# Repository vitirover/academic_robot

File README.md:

# Vitirover Academic Robot

🌿 The Vitirover Academic empowers students and researchers to operate a robot designed for complex outdoor environments, boasting exceptional energy management and a patented, uniquely engineered movement system. We provide detailed motion equations for an in-depth understanding.

## 🕹️ Control Options:

 - __Web Interface__: Intuitively control the robot through our [user-friendly web platform](https://cloud.vitirover.eu).
 - __Remote Scripting__: Use Scratch-like interface to program and execute remote scripts.
 - __Advanced Mode__: For the tech-savvy, dive into __Python__ coding or __ROS__ for granular control.

## 🔧 What's inside

 - Standard Vitirover Robot
 
 - Charger
 
 - Alimentation card to add you own electronics, detectors or motors. More information [here](./power_card/).

 - Jetson Nano : to operate the robot directly with your code. You could use any board (raspberry, etc.), but documentation will be provided for Jetson 

## 📡 API Features

Protobuf Technology: Utilizes Google's Protobuf for standardized, cross-language communication protocol encoding and decoding.

Data Frames:
 - __Telemetry Data__: Broadcasted by the robot at 10Hz, includes GPS, rear axle angle, motors status, and more.
 
 - __Control Commands__: Send direct instructions for individual motor control.

You can keep the two cameras connected to our electronics, or connect them to your board if you want to use Vision in you application.

The trame definitions with all fields are [here](protobuf/telemetry.proto)

# Getting started

## With the standard Vitirover web interface

 - Get a Vitirover robot through us or our distributors

 - Get a [Vitirover Cloud account](https://cloud.vitirover.eu) connected to this robot by first creating you account and contacting us to add the robot to your account

 - Push the Vitirover On/Off button at the back upward

 - Wait for the robot to connect. Its icon will turn yellow 🟡

 - In your robot page (click its name on the menu), you should be able to move the robot using the controller 🎮 icon on the map

  - You can activate the robot live view from its camera using the camera icon on the map 👁️ (only if cameras are connected to the main board)

 - In the Scripts section, try out Scratch-like scripts. Use Control blocks to move the robot. Experiment, but ensure the robot is on the ground to prevent falls.⚠️

 - Please consult the Vitirover help section in our cloud for using the standard robot functions ❓

## With the Jetson Nano included in the Academic robot

### Using SSH and a local network

The **VitiroverAP_[name of your robot]** network is intended for private use since it is emitted by our non-academic motherboard.

Starting at this commit, we include a **vitirover-wifi-manager** systemd service to help you getting remote access without the need to open the robot each time (see "direct access" section). When a wifi configuration is set up, it will be active even after a reboot.
The Jetson Nano, with the Wifi card we added, only supports one wifi connection at the time. But to be able to use this connection confortably, you will need to have an SSH connection and an internet access on the Jetson Nano simultaneously.
In order to accomplish this, the solution is to connect the Jetson Nano directly to your local wifi network, and get SSH access from your computer thought your local wifi network.

#### If vitirover-wifi-manager is installed (robots produced since this commit)

The "vitirover-wifi-manager" emits a hotspot network, **Vitirover-SSH**. Thought this network, you will configure the **local network** you want to use. Once this is done, you apply this configuration, SSH will cut, and you will be able to access SSH again thought your local-network.

- Start the robot and the Jetson Nano
- Connect to the **Vitirover-SSH** network. Password is **vitirover**
- use putty (on windows) or ssh on "vitirover@10.42.0.1" (port 22).
- cd ~/Desktop/academic_robot/
- sudo ./wifi_config_tools config
- follow instructions to configure your local wifi network to connect to (using a static ip address)
- reboot, the robot should be connected to your local wifi network using the IP adress you provided
- connect to the robot thought you local network with SSH (user and password are vitirover, port 22). Now you should have both a working SSH connection, AND access to internet (ping 8.8.8.8 to check)
- see python examples or ros repository (or installation folder where there are some examples) to begin

#### If vitirover-wifi-manager is not installed yet
You will have to use get direct access to the jetson nano (see next section), then : 
 - cd ~/Desktop/academic_robot/
 - git pull (or "git switch wifi-manager" if not merged yet)
 - cd vitirover-wifi-manager
 - chmod +x wifi_config_tools
 - chmod +x vitirover-wifi-manager
 - sudo ./wifi_config_tools install
 - sudo ./wifi_config_tools config
 - follow instructions to configure your local wifi network to connect to (using a static ip address)
 - reboot, the robot should be connected to your local wifi network
 - connect to the robot thought you local network with SSH (user and password are vitirover, port 22). Now you should have both SSH connection, AND access to internet (ping 8.8.8.8 to check)
- see python examples or ros repository to begin

### Direct access to the Jetson nano

If you struggle with the setup of the SSH connection and remote access, you can always connect directly on the jetson nano by : 
 - removing the ten screws with a M5 Allen Key (found on bike repair kits for example). Pay attention to not pull cables (GNSS antenna and power cable). It is practical to keep the upper hull on top, but turn it to access the Jetson Nano.
 - checking that the robot is on (button is up) and leds on the Jetson Nano are on
 - Connecting a computer screen via a Jetson HDMI port
 - Connecting a USB mouse, a keyboard to the Jetson
 - Log in : The default user and password is __vitirover__.****
 - This repository, and the [ROS repository](https://github.com/vitirover/vitirover_ws) are already present. If they are not up to date, you can do a **git pull** on them. 
 - In order to start, you can for example test python example scripts in examples, or head directly into the [ROS repository](https://github.com/vitirover/vitirover_ws)

### Network Schema
**Coming soon**

# Python example scripts

In order to control the robot directly from you code, you will need the Jetson Nano connected throught an USB/Ethernet adapter to our electronics JST ports.

See [the python basic example](/examples/basic-python-protobuf.py)

# Getting started: Jetson Nano

In the academic package you have a Jetson nano included. A Linux OS as well as some examples to use the robot are already pre-installed. 
If you want more informations on how to install your own setup you can refer to : [Nvidia](https://developer.nvidia.com/embedded/learn/get-started-jetson-nano-devkit#intro)

The password by default is "vitirover". Once you are logged in you can open Visual Studio Code (exactly : code-oss, the full open-source version) and navigate to academic_robot/examples. 

# How to use the Jetson nano remotely
## On Linux

In your package you can find a fake HDMI. This dongle allows you to visualize your Jetson Nano from your PC through the wifi card (that we added to the standard Jetson Nano). 

First, connect the Jetson Nano to your wifi. 

Install tightvnc on your PC (do it once only):
```
sudo apt install xtightvncviewer
```

Then start the server (modify your.ip.address with your IP address):

```
xtightvncserver your.ip.address
```
or 
```
/usr/bin/xtightvncserver your.ip.address
```

Connect to the jetson nano:
```
xtightvncviewer your.ip.address -compresslevel 9 -quality 4
```

Type your password, and you are logged into the Jetson Nano ;)

## Counter EMF to measure motor's rpm

The agricultural standards require high robustness due to operation in chaotic terrain. To measure the RPM of the wheels, we have utilized Back Electromotive Force (BEMF), which provides accurate RPM measurements suitable for outdoor environments. For academic purposes, an encoder kit is available, offering even more precise RPM measurements. For more information about the encoder kit, please visit [encoder kit](/encoder_kit).

# Contributing

We would be glad to hear from you, you contact us via issues for any questions about this repo.

This repository is constently evolving with new updates and more examples. Feel free to contribute to our community on the academic robot !

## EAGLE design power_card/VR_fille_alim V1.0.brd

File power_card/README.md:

## Power Board Overview 🌐

The power board features four terminal blocks, each providing a different maximum output voltage and current. Here are the specifications and maximum power calculations for each:

- **12V, 2A**  
  Maximum Power: `24W`
- **5V, 2A**  
  Maximum Power: `10W`
- **5V, 4A** (dedicated for powering the Jetson Nano, see above)  
  Maximum Power: `20W`
- **Battery Voltage (24V nominal), 6A**  
  Maximum Power: `144W`

Additionally, links to the EAGLE files for the power board are provided. These files include all necessary schematics and board designs in EAGLE format, ideal for modification or further development.

### Jetson Nano DC Power Jumper

As explained (but difficult to find) in the [Jetson Nano Developper Kit User Guide](https://developer.download.nvidia.com/assets/embedded/secure/jetson/Nano/docs/NV_Jetson_Nano_Developer_Kit_User_Guide.pdf?onc0KLg5WqXnycWsVxITqVJuQhOv7dOwZDn_6wMDd2yiHHP-d7uv_KwyZQFvdmQjeIwzmvuDMyNS2j6b7665m7rmn-Uv2NYOiBAWWCoRhCM5Xq7rqr0AOUHEIOBn2JpZgTdjgMTqyD2t5OOGEKS2ve_BtuEa8IP3TMF1NwbBa36ZujDmUTJMczagMmcFHalibv8=&t=eyJscyI6ImdzZW8iLCJsc2QiOiJodHRwczovL3d3dy5nb29nbGUuY29tLyJ9) and [on the jetson forum](https://forums.developer.nvidia.com/t/power-supply-considerations-for-jetson-nano-developer-kit/71637), for versions of the Jetson Nano with a Barrel Jack, you have to **connect the jumper** to the J48 pins to be able to power the board from this power supply. We connect it to ensure that everything is working before shipping the robot to you.
Similarly, if you want to power the Jetson from another power source, you have to **disconnect** the jumper.

### Safety Warning ⚠️

**Current Limitation:** The total current consumption across all systems connected to the board must not exceed 6A. Exceeding this limit will trigger a protective fuse, rendering the power board unusable.

**Connection Precautions:** It is crucial to follow the markings on the PCB. Ensure that the positive and negative terminals (GND) are not reversed when connecting any system to the terminal blocks.

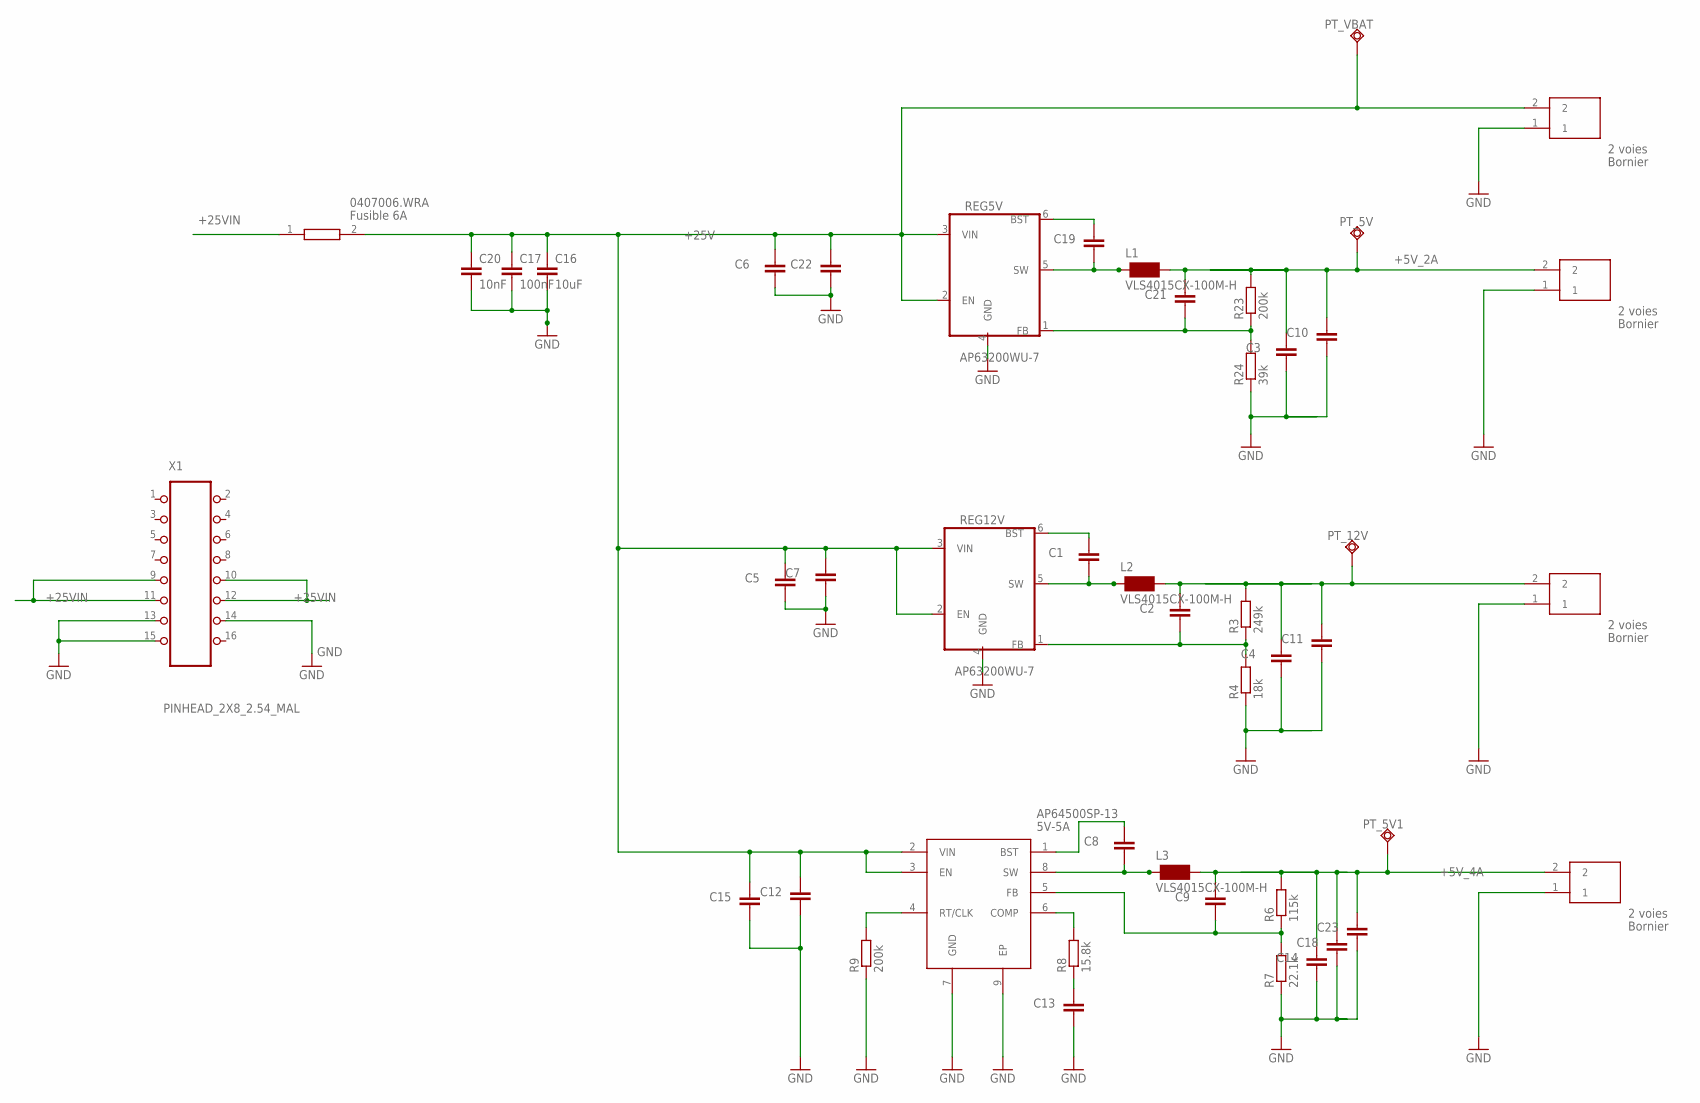
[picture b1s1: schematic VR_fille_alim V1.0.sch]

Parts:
C1, C5, C6, C8, C15, C19: 100nF; C0402
C2: 56pF; C0402
C3, C4, C10, C11, C14, C18, C23: 22uF; C0402
C7, C12, C22: 10uF; C0402
C9, C21: 100pF; C0402
C13: 2.7nF; C0402
C16: 10uF; C0805
C17: 100nF; C0805
C20: 10nF; C0805
F1: 0407006.WRA; FUSC3216X98N
IC1: AP64500SP-13; SOIC127P600X163-9N
J1, J2, J3, J5: 691214110002
L1, L2, L3: VLS4015CX-100M-H; VLS4015
PT_5V, PT_5V1, PT_12V: POINT_TEST
PT_VBAT: POINT_TEST
R3: 249k; R0402
R4: 18k; R0402
R6: 115k; R0402
R7: 22.1k; R0402
R8: 15.8k; R0402
R9, R23: 200k; R0402
R24: 39k; R0402
REG5V, REG12V: AP63200WU-7; TSOT26
X1: PINHEAD_2X8_2.54_MAL

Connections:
+5V_2A: C3.2, C10.2, C21.2, J1.2, L1.2, PT_5V.>NAME, R23.2
+5V_4A: C9.2, C14.2, C18.2, C23.2, J3.2, L3.2, PT_5V1.>NAME, R6.2
+12V_2A: C2.2, C4.2, C11.2, J2.2, L2.2, PT_12V.>NAME, R3.2
+25V: C5.2, C6.2, C7.2, C12.2, C15.2, C16.1, C17.1, C20.1, C22.2, F1.2, IC1.2 (VIN), IC1.3 (EN), J5.2, PT_VBAT.>NAME, REG5V.2 (EN), REG5V.3 (VIN), REG12V.2 (EN), REG12V.3 (VIN)
+25VIN: F1.1, X1.9, X1.10, X1.11, X1.12
GND: C3.1, C4.1, C5.1, C6.1, C7.1, C10.1, C11.1, C12.1, C13.1, C14.1, C15.1, C16.2, C17.2, C18.1, C20.2, C22.1, C23.1, IC1.7 (GND), IC1.9 (EP), J1.1, J2.1, J3.1, J5.1, R4.1, R7.1, R9.1, R24.1, REG5V.4 (GND), REG12V.4 (GND), X1.13, X1.14, X1.15
unnamed: C2.1, R3.1, R4.2, REG12V.1 (FB)
unnamed: C1.1, L2.1, REG12V.5 (SW)
unnamed: C1.2, REG12V.6 (BST)
unnamed: C9.1, IC1.5 (FB), R6.1, R7.2
unnamed: C8.1, IC1.8 (SW), L3.1
unnamed: C8.2, IC1.1 (BST)
unnamed: IC1.6 (COMP), R8.2
unnamed: C13.2, R8.1
unnamed: C21.1, R23.1, R24.2, REG5V.1 (FB)
unnamed: C19.1, L1.1, REG5V.5 (SW)
unnamed: C19.2, REG5V.6 (BST)
unnamed: IC1.4 (RT/CLK), R9.2

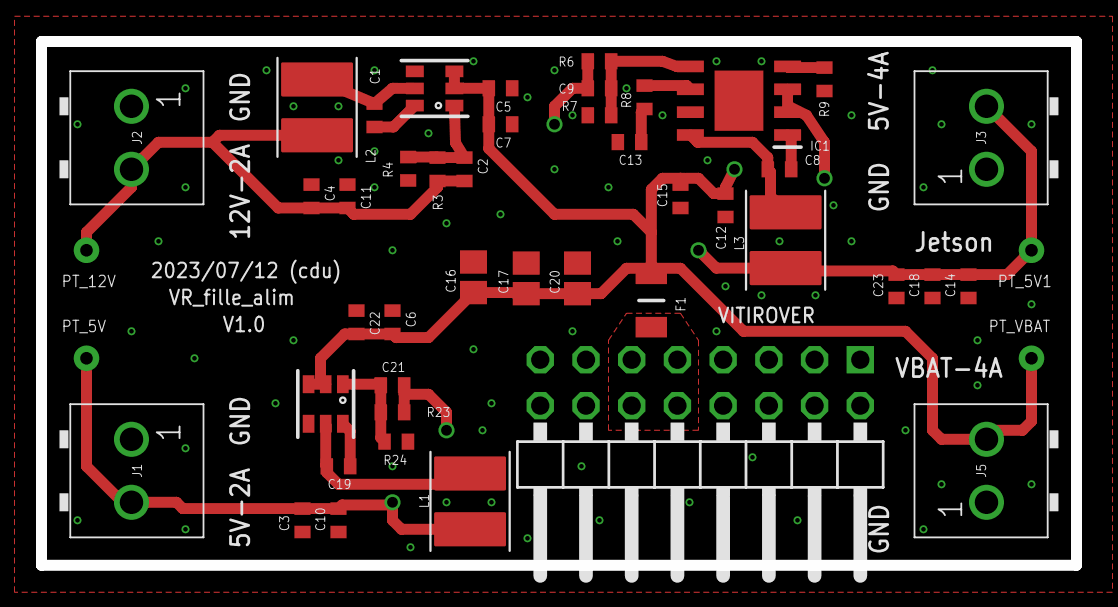
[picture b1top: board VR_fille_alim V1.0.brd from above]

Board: 4 copper layers, 57.5 x 29.1 mm, 47 parts (0 on the bottom side), 18 nets.

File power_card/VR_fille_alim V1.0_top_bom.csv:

Comment,Designator,Footprint,LCSC Part #
2.7nF,C13,C0402,
10nF,C20,C0805,
10uF,C7 C12,C0402,
10uF,C16,C0805,
10uF,C22,C0402,
15.8k,R8,R0402,
18k,R4,R0402,
22.1k,R7,R0402,
22uF,C3 C4 C10 C11 C14 C18 C23,C0402,
39k,R24,R0402,
56pF,C2,C0402,
100nF,C1 C5 C6 C8 C15,C0402,
100nF,C17,C0805,
100nF,C19,C0402,
100pF,C9 C21,C0402,
115k,R6,R0402,
200k,R9 R23,R0402,
249k,R3,R0402,
0407006.WRA,F1,FUSC3216X98N,
AP63200WU-7,REG5V REG12V,TSOT26,
AP64500SP-13,IC1,SOIC127P600X163-9N,
VLS4015CX-100M-H,L1 L2 L3,VLS4015,
691214110002,J1 J2 J3 J5,691214110002
PINHEAD_2X8_2.54_MAL,X1,PINHEAD_2X8_2.54_MAL

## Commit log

2023-10-04 Create telemetry.proto for communicating with the robot
2023-10-06 first test on communication
2023-10-06 Create VRwheel.urdf.xacro
    Adding the xacro file for the wheels of the vitirover urdf
2023-10-06 Create vitirover.urdf.xacro
    Adding the urdf of the vitirover
2023-10-06 Create vitirover_gazebo.urdf
    Urdf for the gazebo simulation
2023-10-10 working basic python example
2023-10-12 lire plusieurs messages en même temps pour réduire la latence
2023-10-12 ajout de commandes wheels
2023-10-17 added telemetry for IMU raw data
2024-01-19 added protobuf generated file
2024-01-19 work
2024-01-22 redaction
2024-02-02 Update README.md
    Added the vitirover in gazebo image
2024-03-08 Update command_wheels.py
    Updated the IP for the robot
2024-05-15 Added a picture of the academic power card
2024-05-15 Added a README for the power board
2024-05-15 added gerber, bom
2024-05-15 typos and added a link for the power board
2024-06-21 added a photo a the J48 jetson nano jumper
2024-06-21 added Jumper details for powering the Jetson Nano
2024-06-21 use python3, not python :-/
2024-06-21 comments about the IP address
2024-06-21 added protobuf. pygame not working
2024-06-24 precision : code-oss is installed, not vscode
2024-06-30 install ros-melodic-teleop-twist-keyboard
2024-06-30 ajout du test de ROS
2024-06-30 install rospkg
2024-07-22 Ajout de précisions sur la jetson nano Okdo
2024-07-26 added VitiroverMowerOrder
2024-07-26 executed protoc
2024-07-26 rotation_per_minute => rotations_per_minute meter => meters_per_hour. begin by left mower
2024-09-13 added catkin_make and source devel/setup.bash to the test protocol
    added catkin_make and source devel/setup.bash to the test protocol. And a few text changes.
2024-09-17 Create installation_commands_auto.sh to fully automatique jetson installation
2024-09-17 no sudo in installation_commands
2024-09-17 bashrc should be sourced as much as possible
2024-09-17 finally going back to code-oss
2024-09-17 adding code-oss icon
2024-09-18 source bashrc is useless in a non-interactive script
2025-06-13 Update ssh_config.md for network manager
2025-06-20 added instructions to access the jetson and the vitirover-wifi-manager.
2025-06-20 added instructions on how to use vitirover-wifi-manager
2025-06-20 added instructions for wifi-manager
2025-06-23 Update README.md typo
